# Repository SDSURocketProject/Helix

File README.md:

# Helix

Coming Soon(TM)

(C) 2019

# Todo
* Build the Helix System.

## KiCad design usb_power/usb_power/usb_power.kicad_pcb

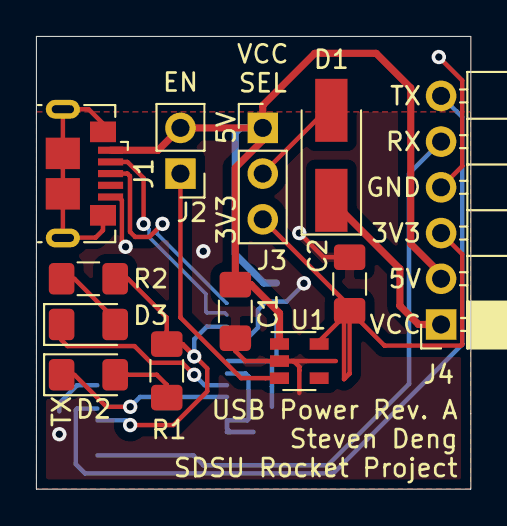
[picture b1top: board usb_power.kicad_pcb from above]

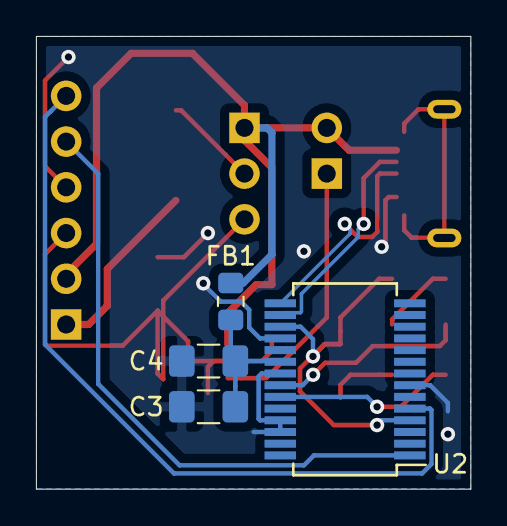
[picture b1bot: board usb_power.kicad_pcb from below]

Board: 2 copper layers, 24.1 x 25.1 mm, 16 parts (4 on the bottom side), 16 nets.

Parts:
C1, C2, C3: 10uF; C_1206_3216Metric_Pad1.42x1.75mm_HandSolder
C4: 0.1uF; C_1206_3216Metric_Pad1.42x1.75mm_HandSolder
D1: B140-13-F; D_SMA_Handsoldering
D2, D3: LED; LED_1206_3216Metric_Pad1.42x1.75mm_HandSolder
FB1: Ferrite_Bead_Small; R_0805_2012Metric_Pad1.15x1.40mm_HandSolder
J1: USB_B_Micro; USB_Micro-B_GCT_USB3076-30-A
J2: Conn_01x02; PinHeader_1x02_P2.54mm_Vertical
J3: Conn_01x03; PinHeader_1x03_P2.54mm_Vertical
J4: Conn_01x06; PinSocket_1x06_P2.54mm_Horizontal
R1, R2: 330; R_1206_3216Metric_Pad1.42x1.75mm_HandSolder
U1: TLV75533PDBV; SOT-23-5
U2: FT232RL; SSOP-28_5.3x10.2mm_P0.65mm

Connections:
+3V3: C2.1, J3.3, J4.3, U1.5
+5V: C1.1, FB1.2, J1.1, J2.2, J3.1, J4.2, U1.1
/FT232_3V3_OUT: R1.1, R2.1, U2.4, U2.17
/RXLED: D3.1, U2.22
/TARGET_RX: J4.5, U2.1
/TARGET_TX: J4.6, U2.5
/TXLED: D2.1, U2.23
/USB_D+: J1.3, U2.15
/USB_D-: J1.2, U2.16
GND: C1.2, C2.2, C3.2, C4.2, J1.5, J4.4, U1.2, U2.7, U2.18, U2.21, U2.25, U2.26
unnamed: C3.1, C4.1, FB1.1, U2.20
unnamed: D1.2, J3.2
unnamed: D2.2, R1.2
unnamed: D3.2, R2.2
unnamed: J2.1, U1.3
VCC: D1.1, J4.1

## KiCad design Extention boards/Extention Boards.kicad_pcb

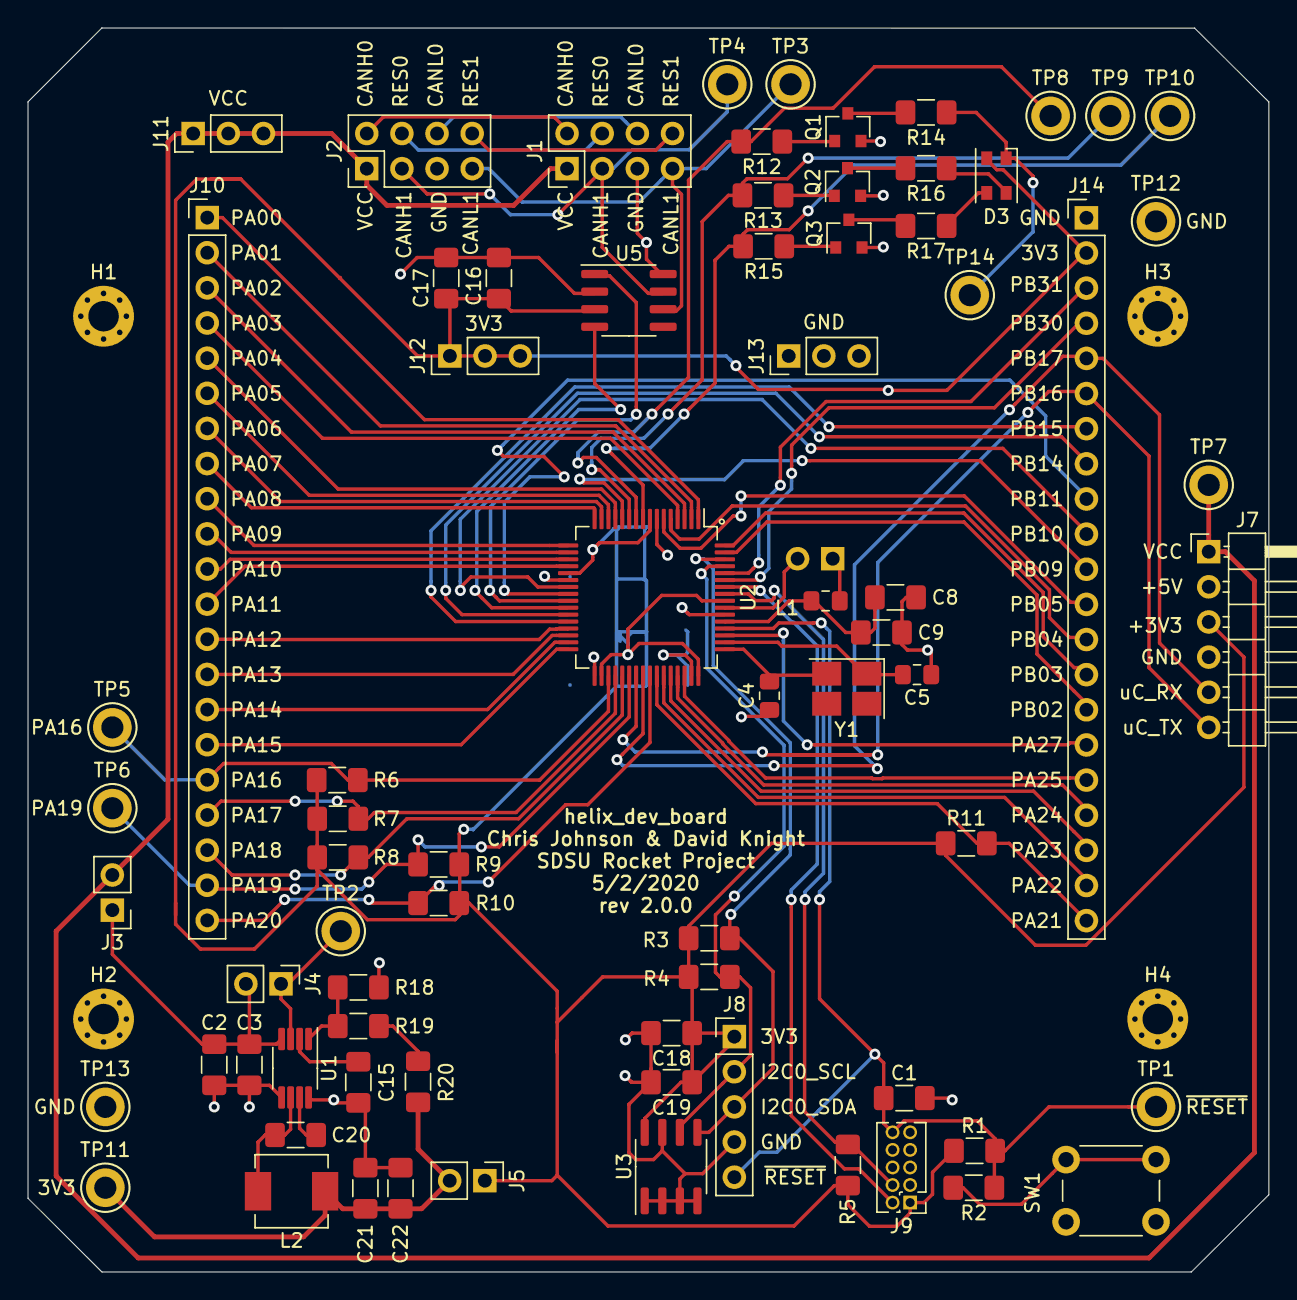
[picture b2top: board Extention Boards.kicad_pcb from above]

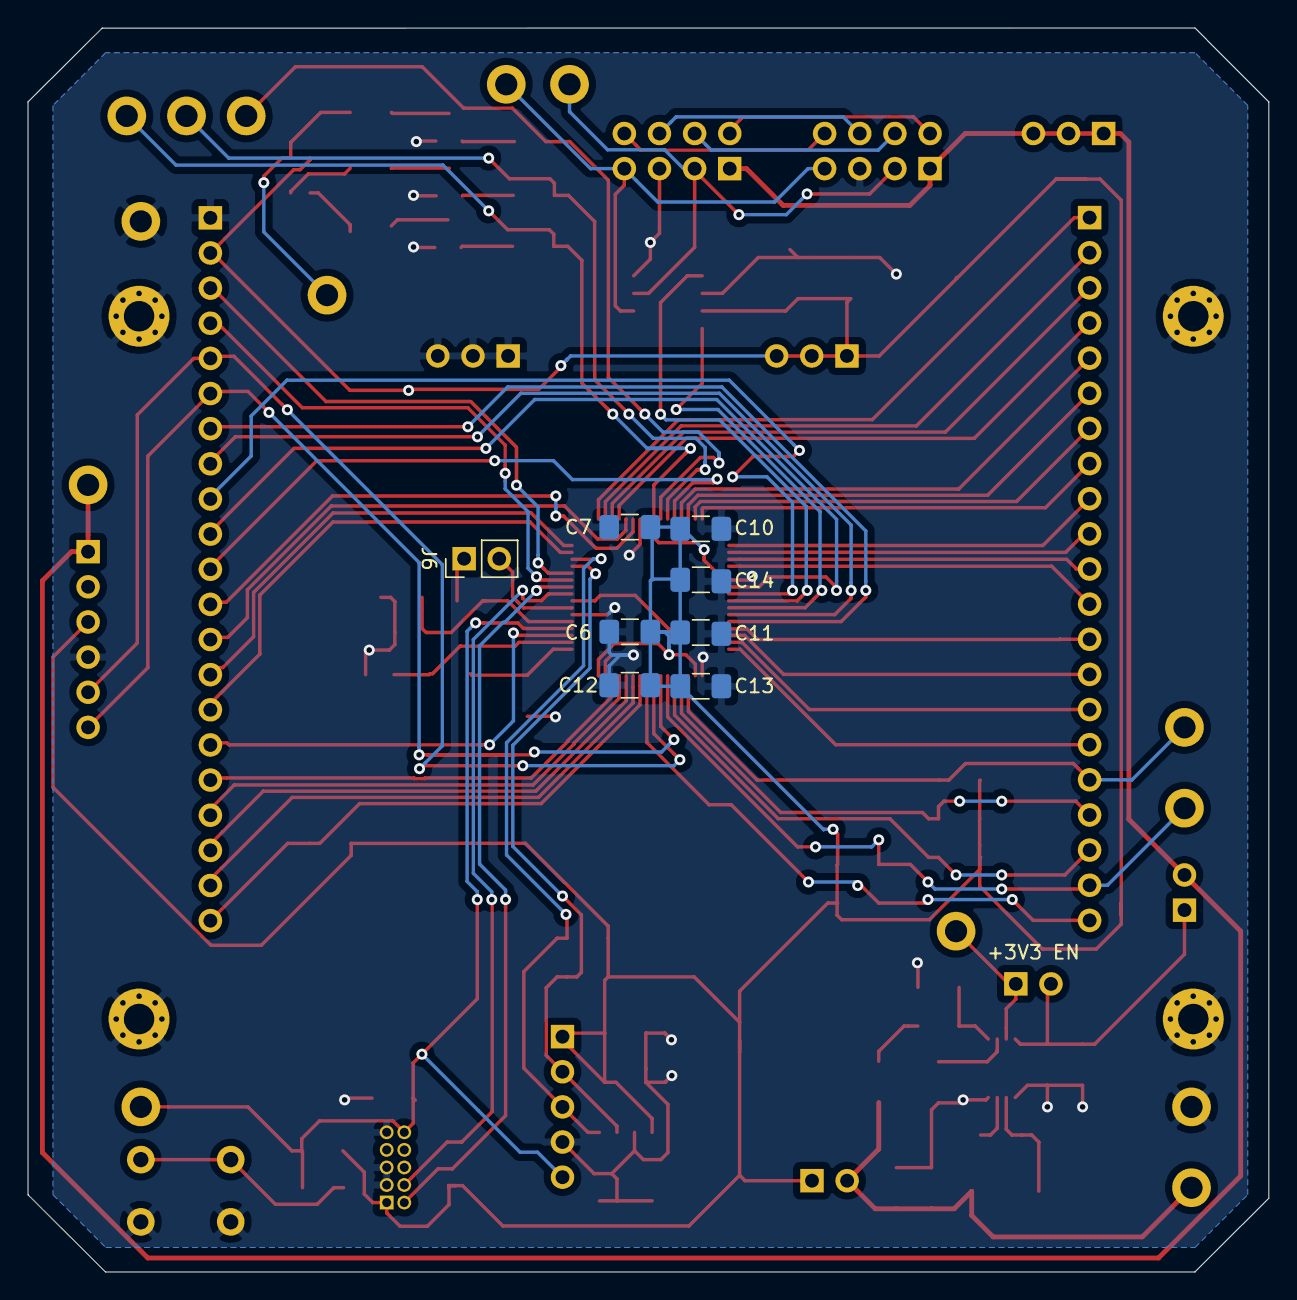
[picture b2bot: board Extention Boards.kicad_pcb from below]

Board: 2 copper layers, 89.7 x 89.9 mm, 86 parts (8 on the bottom side), 82 nets.

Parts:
C1, C17, C19: .1uF; C_1206_3216Metric_Pad1.42x1.75mm_HandSolder
C2, C3, C10, C11, C16, C18, C21, C22: 10uF; C_1206_3216Metric_Pad1.42x1.75mm_HandSolder
C4, C5: 9pF; C_0805_2012Metric_Pad1.15x1.40mm_HandSolder
C6, C7, C9, C12, C13, C14: 0.1uF; C_1206_3216Metric_Pad1.42x1.75mm_HandSolder
C8: 4.7uF; C_1206_3216Metric_Pad1.42x1.75mm_HandSolder
C15: 1uF; C_1206_3216Metric_Pad1.42x1.75mm_HandSolder
C20: 100nF; C_1206_3216Metric_Pad1.42x1.75mm_HandSolder
D3: LED_RABG; LED_Cree-PLCC4_3.2x2.8mm_CCW
H1, H2, H3, H4: MountingHole_Pad; MountingHole_2.2mm_M2_Pad_Via
J1, J2: Conn_02x04_Top_Bottom; PinHeader_2x04_P2.54mm_Vertical
J3, J4, J5, J6: Conn_01x02; PinHeader_1x02_P2.54mm_Vertical
J7: Conn_01x06; PinHeader_1x06_P2.54mm_Horizontal
J8: Conn_01x05; PinHeader_1x05_P2.54mm_Vertical
J9: Conn_02x05_Odd_Even; PinHeader_2x05_P1.27mm_Vertical
J10, J14: Conn_01x21; PinHeader_1x21_P2.54mm_Vertical
J11, J12, J13: Conn_01x03; PinHeader_1x03_P2.54mm_Vertical
L1: 10uH; L_0805_2012Metric_Pad1.15x1.40mm_HandSolder
L2: 15uH; L_Vishay_IHLP-2020
Q1, Q2, Q3: MMBT3904; SOT-23
R1, R20: 27k; R_1206_3216Metric_Pad1.42x1.75mm_HandSolder
R2: 820; R_1206_3216Metric_Pad1.42x1.75mm_HandSolder
R3, R4, R5, R6, R7, R8, R9, R10, R11, R12, R13, R15, R19: 4.7k; R_1206_3216Metric_Pad1.42x1.75mm_HandSolder
R14, R16, R17: 470; R_1206_3216Metric_Pad1.42x1.75mm_HandSolder
R18: 10k; R_1206_3216Metric_Pad1.42x1.75mm_HandSolder
SW1: SW_Push; SW_PUSH_6mm_h4.3mm
TP1, TP2, TP3, TP4, TP5, TP6, TP7, TP8, TP9, TP10, TP11, TP12, TP13, TP14: TestPoint; TestPoint_Keystone_5010-5014_Multipurpose
U1: MCP16311MS; MSOP-8_3x3mm_P0.65mm
U2: ATSAME51J20A; TQFP-64_10x10mm_P0.5mm
U3: CAT24C256; SOIC-8_3.9x4.9mm_P1.27mm
U5: SN65HVD233D; SOIC-8_3.9x4.9mm_P1.27mm
Y1: 16MHz; Crystal_SMD_SeikoEpson_TSX3225-4pin_3.2x2.5mm_HandSoldering

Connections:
+3V3: C6.1, C7.1, C10.1, C11.1, C12.1, C13.1, C14.1, C16.1, C17.1, C18.1, C19.1, D3.2, J5.1, J7.3, J8.1, J9.1, J12.1, J12.2, J12.3, J14.2, R1.1, R3.1, R4.1, R5.1, R6.1, R7.1, R8.1, R9.1, R10.1, R11.1, U2.8, U2.21, U2.34, U2.48, U2.56, U3.8, U5.3
/CANH0: J1.2, J2.2
/CANH1: J1.3, J2.3, TP4.1, U5.7
/CANL0: J1.6, J2.6
/CANL1: J1.7, J2.7, TP3.1, U5.6
/MCU/CAN1_RX: U2.26, U5.4
/MCU/CAN1_TX: U2.25, U5.1
/MCU/I2C0_SCL: J8.2, R4.2, U2.61, U3.6
/MCU/I2C0_SDA: J8.3, R3.2, U2.62, U3.5
/MCU/LED_B: R15.2, TP10.1, U2.9
/MCU/LED_G: R13.2, TP9.1, U2.11
/MCU/LED_R: R12.2, TP8.1, U2.10
/MCU/PA00: J10.1, U2.1
/MCU/PA01: J10.2, U2.2
/MCU/PA02: J10.3, U2.3
/MCU/PA03: J10.4, U2.4
/MCU/PA04: J10.5, U2.13
/MCU/PA05: J10.6, U2.14
/MCU/PA06: J10.7, U2.15
/MCU/PA07: J10.8, U2.16
/MCU/PA08: J10.9, U2.17
/MCU/PA09: J10.10, U2.18
/MCU/PA10: J10.11, U2.19
/MCU/PA11: J10.12, U2.20
/MCU/PA12: J10.13, U2.29
/MCU/PA13: J10.14, U2.30
/MCU/PA14: J10.15, U2.31
/MCU/PA15: J10.16, U2.32
/MCU/PA16: J10.17, R6.2, TP5.1, U2.35
/MCU/PA17: J10.18, R7.2, U2.36
/MCU/PA18: J10.19, R8.2, U2.37
/MCU/PA19: J10.20, R9.2, TP6.1, U2.38
/MCU/PA20: J10.21, R10.2, U2.41
/MCU/PA21: J14.21, R11.2, U2.42
/MCU/PA22: J14.20, U2.43
/MCU/PA23: J14.19, U2.44
/MCU/PA24: J14.18, U2.45
/MCU/PA25: J14.17, U2.46
/MCU/PA27: J14.16, U2.51
/MCU/PB02: J14.15, U2.63
/MCU/PB03: J14.14, U2.64
/MCU/PB04: J14.13, U2.5
/MCU/PB05: J14.12, U2.6
/MCU/PB09: J14.11, U2.12
/MCU/PB10: J14.10, U2.23
/MCU/PB11: J14.9, U2.24
/MCU/PB14: J14.8, U2.27
/MCU/PB15: J14.7, U2.28
/MCU/PB16: J7.6, J14.6, U2.39
/MCU/PB17: J7.5, J14.5, U2.40
/MCU/PB30: J14.4, U2.59
/MCU/PB31: J14.3, U2.60
/MCU/SWCLK: J9.4, R5.2, U2.57
/MCU/SWDIO: J9.2, U2.58
/MCU/VSW: J6.2, U2.55
/RESERVED0: J1.4, J2.4
/RESERVED1: J1.8, J2.8
GND: C1.2, C2.2, C3.2, C4.1, C5.1, C6.2, C7.2, C8.2, C9.2, C10.2, C11.2, C12.2, C13.2, C14.2, C15.2, C16.2, C17.2, C18.2, C19.2, C21.2, C22.2, H1.1, H2.1, H3.1, H4.1, J1.5, J2.5, J7.4, J8.4, J9.3, J9.5, J9.9, J13.1, J13.2, J13.3, J14.1, Q1.2, Q2.2, Q3.2, R18.2, SW1.1, TP12.1, TP13.1, U1.5, U1.8, U2.7, U2.22, U2.33, U2.47, U2.54, U3.1, U3.2, U3.3, U3.4, U3.7, U5.2, U5.8
unnamed: C2.1, C3.1, J3.1, J4.2, U1.4
unnamed: C4.2, U2.49, Y1.2
unnamed: C5.2, U2.50, Y1.1
unnamed: C8.1, C9.1, L1.1, U2.53
unnamed: C15.1, U1.2
unnamed: C20.1, L2.1, U1.6
unnamed: C20.2, U1.7
unnamed: C21.1, C22.1, J5.2, L2.2, R20.2, TP11.1
unnamed: D3.1, R14.1, TP14.1
unnamed: D3.3, R17.1
unnamed: D3.4, R16.1
unnamed: J4.1, TP2.1, U1.3
unnamed: J6.1, L1.2
unnamed: Q1.1, R12.1
unnamed: Q1.3, R14.2
unnamed: Q2.1, R13.1
unnamed: Q2.3, R16.2
unnamed: Q3.1, R15.1
unnamed: Q3.3, R17.2
unnamed: R2.2, SW1.2
unnamed: R18.1, R19.1, U1.1
unnamed: R19.2, R20.1
VCC: J1.1, J2.1, J3.2, J7.1, J11.1, J11.2, J11.3, TP7.1
~RESET: C1.1, J8.5, J9.10, R1.2, R2.1, TP1.1, U2.52

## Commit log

2019-07-10 Created new Extention Boards project
2019-07-12 Added new components library
2019-07-12 Removed extra cat24c256 library
2019-07-12 Created Power and MCU sections
2019-07-12 Added some power out protection
2019-07-12 Added now symbol for INA4180 and created power channels
2019-07-12 Imported pins on root sheet
2019-07-13 Added new labels on MCU page
2019-07-14 Added a bunch of stuff
2019-07-14 Re-annotated schematic
2019-07-14 Replaces 8x1 muxes and added some resistor values
2019-07-15 Fixed ERC errors
2019-09-04 Made a lot of changes
2019-09-05 Updated schematic to kicad v5 and made minor cosmetic changes
2019-09-19 Added SAMC21J18A to schematic and fixed previous DRC errors
2019-09-24 Changed symbol reference locations and removed ref voltage from AD8495
2019-09-24 Fixed some errors and replotted schematic
2019-09-27 Testing github mirroring
2019-09-27 Corrected location of helix lib
2019-09-27 Corrected bold nets and notes
2019-09-29 updated helix lib with tps2121 and pocketbeagle symbols
2019-10-02 removed TVS diodes, changed reset capacitor to 3.3nF, changed pull-up resistor on SWCLK to 2.7k, changed capacitor on REFOUT of ADS1247 to 10uF
2019-10-15 Added ATSAME51J20A to helix.lib
2019-10-15 made many small changes to schematic, in need of cleanup
2019-10-15 Corrected reoriented pins on ATSAME51J20A
2019-10-15 Converted schematic from 5v to 3.3v and switched uC to SAME51J20A
2019-10-15 Updated .bak files
2019-10-15 Updated annotation and plotted schematic to pdf
2019-10-15 Changed Extention boads from 5v to 3.3v and changed uC from SAMC21 to SAME51
2019-10-25 Added Layout to Project
    Some things to note:
    Need to look at C3 and change it to a polar cap if necessary.
    Should we add more than one 3v3 power rail?
    EEPROM closer to chip?
    TODO:
    check supporting circuitry for ICs (namely power and CAN and EEPROM) to match manufacturers
2019-10-26 Regenerated Schematic
    Schematic still reflected master and needed to be regeneerated so it
    reflected the branch better. This took the schematic from the full board
    of nine pages to 2 pages. The two remaining pages are what the PCB
    layour reflects.
2019-10-27 Reworked Based off of Feedback
    Reworked 3v3 power delivery rail from 9.28 mils thickness to 20mils seeing as it carries power for multiple components
    Added a GND and 3V3 power rail
    Moved the upper connectors and LED circuitry to move D1 in line with transistors
    Changed C17 to be tantalum as a polar Cap was needed rather than a Ceramic This resulted in the package size of C17 changing from 1206 to 0805 to accommodate the new capacitor.
    Bom has been aded to the BOM directory for purchasing.
    Added polarity marker for power input. (J8)
2019-10-28 Added partially complete BOM
    Added BOM with unique parts that are not currently on David's BOM.
    I guarantee the components listed in the BOM have compatible footprints with
    the current layout in this commit.
2019-10-28 initial commit of power distro board
2019-10-29 Changed footprints to match new BOM and corrected minor errors
2019-10-29 Added mounting holes
2019-10-29 Corrected spacing of mounting holes to be 1in apart
2019-10-29 Added pin names next to pin headers
2019-10-29 Added RP logo
2019-10-30 Edited git ignore
    Removed the git-ignore markers for keeping .csv and .xml documents
    untracked. I did this because my BOM was a .csv file type and I wish it
    to be tracked along the course of the project.
2019-10-30 Minor Edits
    Changed size of board to be tad bigger to allow for more space for CAN jumper pin labelings, still very much under 100m x 100m.
    Changed pad whole ID from 2.5 to 3.5mm (M3 screw moderate tolerance)
    Hid hole solder mask indicators
    Added pin one indicators for ICs.
    SW1 -> RST on F. Solder Mask flipped and moved reference indicator
    Hole spacing is now exacly 3 in. wide by 2 in. long. Moved H3 and H4 over since they were close to GPIO rail.
2019-10-30 Increased Text Size
    Increased front text size from 5.9 mils to 7 mils to make sure the board
    house can correcctly make the text legible on the board.
    Word of Caution:
    The bad bitmap of the SDSU Rocket Project logo remains. Needs to be
    removed or updated.
    DRC Passed.
2019-10-30 Removed Bitmap of RP logo
    The logo for RP is too small and too detailed for the board house. In 3D
    view it really does remind you that it is almost halloween.
2019-11-04 Removed TVS diodes and added test points
2019-11-04 Corrected bold text on mcu schematic page
2019-11-05 Modified PT inputs to divide down to 2.5v to be compatible with 3.3v supply
2019-11-05 Corrected minor mitakes in helix symbol library and schematic
2019-11-10 Corrected bold text bug
2019-11-11 Corrected issues with MC33063 schematic
2020-01-03 Add .gitlab-ci.yml
2020-01-10 Added missing 3v3 supply for decoupling caps on SN74LV4052
2020-01-11 Replaced the CAT24C256 with the CAT24C512
    The two components are exactly the same in package and usage, the
    only difference is that the CAT24C512 has twice as much memory. The
    cost difference is small so the extra memory size is worth it.
2020-01-11 Fixed component annotations to not include page number
2020-01-11 Added footprints to components
    The resistor array for the PT inputs on the sensor section was changed
    from a network of 8 resistors to 3 networks of 2 resistors. This is
    cheaper to purchase, there are more products available, and
    accomplishes the same problem as the network of 8.
2020-01-11 Removed all parts not needed for sensor board prototype
2020-01-13 Completed layout and routing of PCB
    Still need to double check component references on bottom side of PCB.
2020-01-13 Verified component references and rearragned components.
    Verified that the components references are next to the proper components
    and that each one is sufficiently unobstructed by open silkscreen areas.
    Also rearranged headers and test points to be in order, ie PT0 PT1 PT2.
2020-01-13 Example layout for getting quote from JLCPCB Assembly
2020-01-14 Changed references of project name to SEB Sensor Prototype Board
2020-01-15 Made initial changes to schematic
2020-01-15 Reorganized headers to get all necessary signals from uC proto board
2020-01-15 Aligned headers on PCB layout to fit to other prototype boards
2020-01-16 Improved decoupling on ICs
    Added 0.1uF decoupling cap to TLV9054.
    Improved locations of decouplinc caps on AD8495 ICs.
    Rearranged traces.
2020-01-18 Made fixed to schematic mistakes and placed components for layout.
    Added power and ground connections for LM339 ICs.
    Placed components for lout and did some minor local routing.
2020-01-19 Completed routing of layout
2020-01-19 Made changes to board silkscreen
    Fixed sizing of silkscreen mask to meet JLCPCB requirements of
    32 mil height and 6 mil line thickness.
    Added board identification to front of PCB.
2020-01-28 Moved references for some components for clarity
2020-02-22 Fixed issues with previous design and add new power input
    - Removed connection between VDDCORE and the 3.3v supply.
    - Added the ability to run the uC in switching mode for more efficiency.
    - Added usb micro connector so the board can be powered off a usb port.
    - Added short-able headers so 5v and 3.3v can be connected to VCC for
    when testing without a 12v power supply.
    - Added multiple test points to make debugging easier.
2020-02-22 Added fix for power OVLD channels and added power flags.
    The proper design for a comparator with hysteresis has pull-up
    resistors on the output of the comparator. However these were forgotten
    on the HELIX_Power_Prototype board, so they can be added here for testing.
    Test points were also added to make it easier to debug the comparator.
    Power flags were added to remove some of the DRC errors, the remaining
    errors require changes to the SAME51J20A symbol.
2020-02-22 Fixed power issue on SAME51J20A
    The VDDCORE pin is actually a voltage output of ~1.2v that is
    intended to supply power to the VSW pin when in Switching mode.
    The SAME51J20A symbol was fixed in the helix symbol library to
    indicate the VDDCORE pin as a voltage output rather than an input
    and the schematic was also changed to reflect the recommended
    power supply setup from the SAME5x datasheet.
2020-02-22 Corrected a mistake on the PWR_CHx_OVLD circuits
    The proper design for a comparator with hysteresis has pull-up
    resistors on the output of the comparator. The current trip
    calculations for the POWER_CHx_OVLD outputs have also been updated
    to reflect the addition of hysteresis that was added awhile ago.
2020-03-17 Modified SAME51J20A symbol to fix DRC errors on VSW pin.
    The VSW pin on the SAME51J20A symbol was incorrectly labeled as a power
    input when it is actually a power output intended to supply power to the
    VDDCORE pin when in switching mode. The schematic was also fixed to remove
    DRC errors caused by this change.
2020-03-25 Created USB power supply
    Created USB-to-3.3V power supply for sensor extension boards.
2020-05-03 Fixed Rev A issues on schematic and updated layout
2020-05-19 Added USB communication to USB Power Board
    Added FT232RL USB-to-UART Transceiver as debug port for TARGET board.
2020-05-21 Added logo to board layout
2020-05-26 Modified schematic for v2, exported gerbers
2020-05-26 Prepared PCB for manufacture
    Replaced USB micro connector with one that is in stock.
    Exported gerbers.
    Added Digikey part numbers to schematic symbols.
    Generated BOM for Digikey.
2020-05-26 Added more silkscreen text to PCB
2020-05-26 Recreated gerbers
2020-05-27 Fixed directory structure that I somehow broke by accident
2020-09-27 Fixed mistakes that were found on uC_ProtoBoard_v2
2020-09-27 Added temperature sensor
2020-09-27 Removed MCP3008 to save board space and cost
    The VCC and current sense measurements have been moved use
    the ADCs on the microcontroller.
2020-09-27 Added 3 additional PTs and removed one HE
    This is to meet SEB requirements for the engine
2020-09-27 Added ADS124S08 and MAX31865
2020-10-05 Moved to new ADC and RTD IC
2020-10-10 New voltage reg, better voltage protection, and consolidated component counts
